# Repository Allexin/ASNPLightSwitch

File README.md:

# ASNPLightSwitch

Light Switch with dimming based on Arduino Pro Mini and ALPS Incremental Encoder EC12D with button

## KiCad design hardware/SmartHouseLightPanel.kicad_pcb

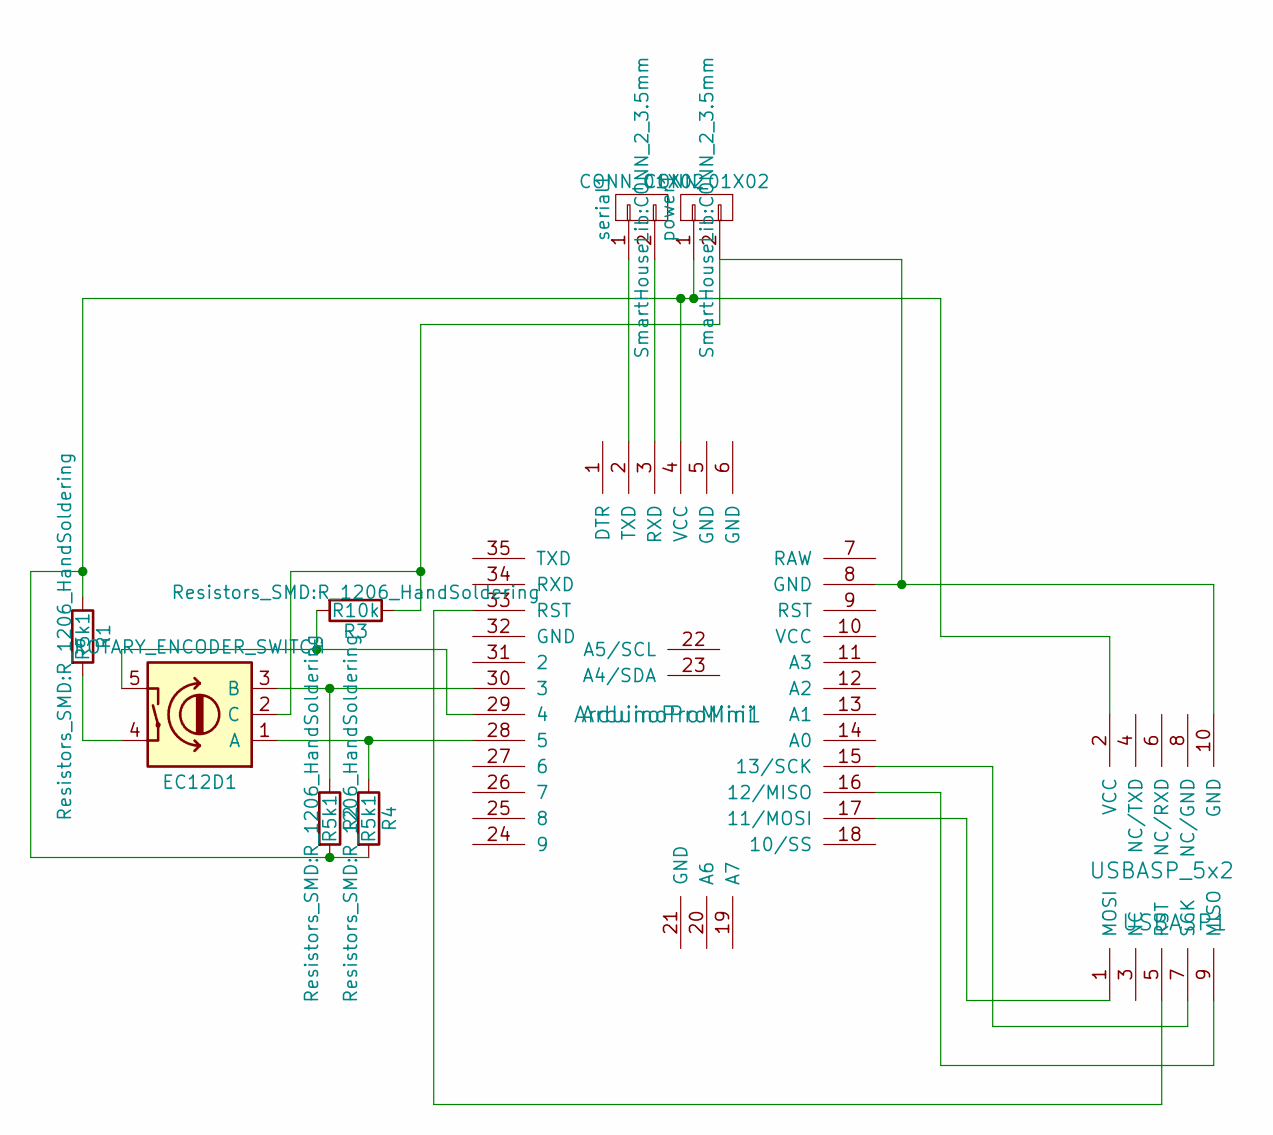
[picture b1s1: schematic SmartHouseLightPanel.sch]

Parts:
ArduinoProMini1: ArduinoProMini
EC12D1: ROTARY_ENCODER_SWITCH; ENCODER_EC12D
R1, R2, R4: R5k1; R_1206_HandSoldering
R3: R10k; R_1206_HandSoldering
USBASP1: USBASP_5x2; Pin_Header_Straight_2x05_Pitch2.54mm
power1: CONN_01X02; CONN_2_3.5mm
serial1: CONN_01X02; CONN_2_3.5mm

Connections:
unnamed: ArduinoProMini1.2 (TXD), serial1.1
unnamed: ArduinoProMini1.3 (RXD), serial1.2
unnamed: ArduinoProMini1.4 (VCC), R1.1, R2.2, R4.2, USBASP1.2 (VCC), power1.1
unnamed: ArduinoProMini1.8 (GND), EC12D1.2 (C), R3.1, USBASP1.10 (GND), power1.2
unnamed: ArduinoProMini1.15 (13/SCK), USBASP1.7 (SCK)
unnamed: ArduinoProMini1.16 (12/MISO), USBASP1.9 (MISO)
unnamed: ArduinoProMini1.17 (11/MOSI), USBASP1.1 (MOSI)
unnamed: ArduinoProMini1.28 (5), EC12D1.1 (A), R4.1
unnamed: ArduinoProMini1.29 (4), EC12D1.5, R3.2
unnamed: ArduinoProMini1.30 (3), EC12D1.3 (B), R2.1
unnamed: ArduinoProMini1.33 (RST), USBASP1.5 (RST)
unnamed: EC12D1.4, R1.2

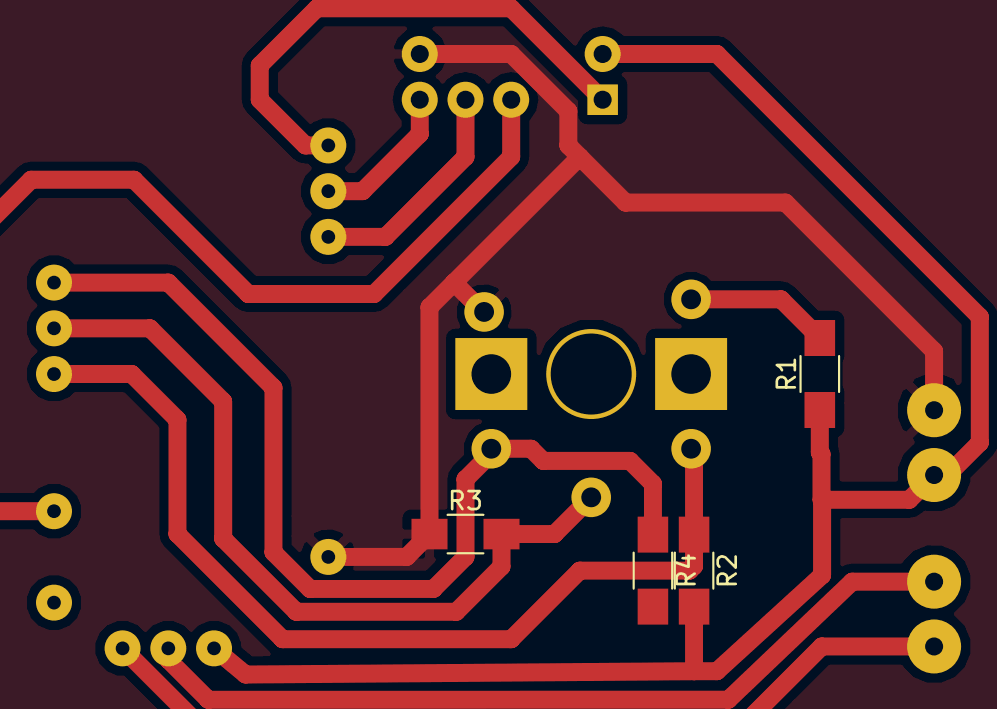
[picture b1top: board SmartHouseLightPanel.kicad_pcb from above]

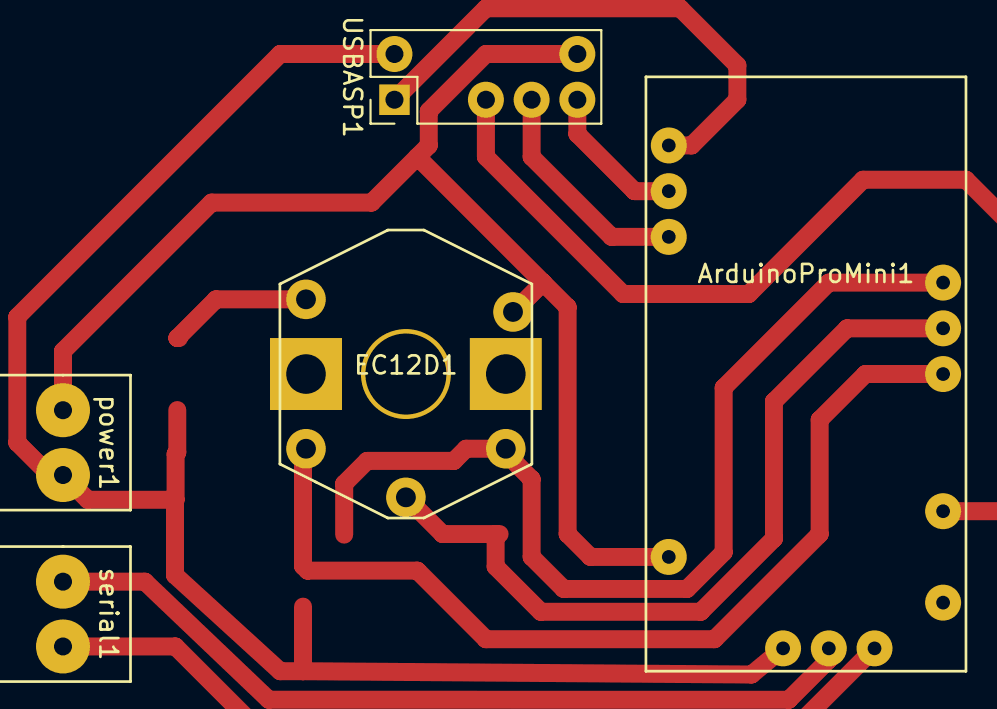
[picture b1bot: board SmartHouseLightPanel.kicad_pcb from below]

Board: 2 copper layers, 9 parts (5 on the bottom side), 12 nets.

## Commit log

2017-12-25 -First release
2017-12-25 -PCB
